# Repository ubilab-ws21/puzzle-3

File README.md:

# Puzzle 3

## Contents
- [Puzzle overview](#puzzle-overview)
- [Repo Structure](#repo-structure)
- [Fitting the Puzzle into the story](#fitting-the-puzzle)
- [Puzzle description](#puzzle-description)
	- [Puzzle Part 1](#Puzzle-1)
	- [Puzzle Part 2](#Puzzle-2)
	- [Puzzle Part 3](#Puzzle-3)
- [MQTT Topics/Specification](#MQTT-Spec)
- [Documents](#documents)

## Puzzle overview

The central role of our puzzle plays a "radio".
The radio consists of a touchscreen display, a speaker, a module to play sound from an sd card, three encoders for tuning as well as one for the volume. The devices are all connected to a ESP32 WROOM Development kit. 
Final aim of the puzzle is to retrieve the so-called "green code" which is needed in a combination to restart the final server, i.e. to succeed in playining the Escape Room. 
It is to be discussed if the radio will maybe deliver more information, e.g. hints for the next puzzle (Morse-Code sound to open the server room door). 
The green code will eventually be displayed on the radio screen, once all the radio-related puzzles have been solved. The puzzles to be solved include the correct positioning of the three encoders which results in a change of the radio station.
The new channel also comes with a new radio display screen. Solving a word game now leads to the final green code. 

## Repo Structure

This repository is structured in the following way:
- datasheets contains all interesting datasheets
- designs contains eagle designs
- code contains the code
- notes cotains all notes from lectures and meetings

## Fitting the Puzzle into the story

The radio belongs to the hobby funker and former power distribution worker Ferdi. 
He has been fired a few years ago due to automatisation and digitalization of the distribution center. Ever since he has been fired, the work in the control room had been done autonomously. Ferdi has always predicted that the full autonoumous room can be dangerous in the future because nobody knows how to fix things if something goes wrong. 

## Puzzle Description 

### Puzzle Part 1 

There is an antenna hidden in the room. When the radio turns on, there is nothing but noise to hear. The players need to find the antenna and plug it into a socket one can find at the radio. This will trigger a button. Also, the correct positioning of the antenna makes a difference which is observed by an encoder insider the radio case. When both is fine, there will be no noise anymore and an emergency broadcast can be heard nicely.

### Puzzle Part 2
A world map is placed in the room. There are three colored pins placed on three diffeents countries pinned on the map. Meanwhile, the screen of the radio shows a three slider bars in the same colors, where the values of each bar can be changed with a correspondingly colored encoder.
Both the radio and the world map belong to the former control room worker, i.e. his name is printed on both the radio case and the world map.
The emergency broadcast plays repeatedly. 
The players must look at the pins on the map, extract the difference of the locations to the greenwich mean time (=delta) and turn the correspondingly colored encoders so that the sliding bars have the deltas as values. When this is done, the Emergency broadcast stops, and instead the voice of the former control room worker, a hobby radio operator, arises. Also the screen changed. The puzzle is solved.

### Puzzle Part 3
In the recording, the former control room worker repeatedly says that he has forseen this and that going away from manual control to autonoumously controlled distribution was a bad choice. 
The screen shows a word puzzle, where it is not clear yet how it looks exactly. From the voice from the radio guy it becomes clear how to solve the puzzle.
After the puzzle was solved, the screen changes again and shows the code which is needed for the next puzzle of the next group (code for opening the door via light bulbs)

## MQTT Topics/Specification

| Topic | Description | Payload | Reset-Value | Subscriber | Publisher |
| :--:	| :---------: | :------:| :---------: |:--------: | :--------:|
| 3/gamecontrol| Control the radio: which puzzle state is currently in play | Enum(Gamecontrol) | idle | radio, operator | radio, operator | 
| 3/antenna/orientation | gives information if the angle of the antenna correct | boolean | false | operator | radio |
| 3/map/knob1 | gives information whether knob1 is in correct position | boolean | false | operator | radio |
| 3/map/knob2 | gives information whether knob2 is in correct position | boolean | false | operator | radio |
| 3/map/knob3 | gives information whether knob3 is in correct position | boolean | false | operator | radio |
| 3/touchgame/trialCount | gives information about the trails the group already had | int | 0 | operator | radio |
| 3/touchgame/displayTime | the game can either be set in easy or hard mode | boolean | false | radio | operator |

3/gamecontrol maybe splitted to received and sended topic. For now we wait for feedback by the operator

| Enum(gameControl) | Description | Subscriber | Publisher |
| :---------------: | :---------: | :--------: | :-------: |
| idle | Radiopuzzle is waiting in idle mode to be started by operator | radio | operator |
| antenna | antenna game is started by operator | radio | operator |
| antennaFinished | antenna game is finished | operator | radio |
| map | map game is started by operator | radio | operator |
| mapFinished | map game is finished | operator | radio |
| touchgame | touchgame is started by operator | radio | operator |
| touchgameFinished | touchgame is finished | operator | radio |
| finished | radio game is finished | operator | radio |

| int(trailCount) | Description |
| :-------------: | :---------: |
| ++ | everytime the game is failed, the trialcounter is increased |

#Topic: 3/gamecontrol

Description: Control the radio: which puzzle state is currently in play

Payload: Enum(Gamecontrol)

Reset-Value: Idle

Enum Values:

# Idle: Radio puzzle is waiting in Idle mode to be started
- Publisher: Operator: set the third puzzle in idle mode
- Subscriber: Radio: receive to stay in idle mode

- antenna: antenna game is started
	Operator: start the first part of the puzzle
	radio: receive to start the puzzle with antenna game
- antennaFinished: antenna game is finished
	Operator: receive updates on the gamestatus
	radio: update once the game is finished

- map: map game is played
	Operator: start the second part of the puzzle
	radio: receive to start the second part of the puzzle
- mapFinished: map game is finished
	Operator: receive updates on the gamestatus
	radio: update once the game is finished

- touchgame: touchgame is played
	Operator: start the third part of the puzzle
	radio: receive to start the third part of the puzzle
- touchgameFinished: touchgame is finished
	Operator: receive updates on the game status
	radio: update once the game is finished

- finished: puzzle 3 is solved
	Operator: set the third puzzle in finished mode
	radio: receive to get in finished mode

<!--Topic: 3/antenna/plugStatus

#Description: gives information about the antenna

% Payload: boolean

Reset-Value: false
	Radio: update if antenna is plugged in
	Operator: receive updates on the antenna-->
	
Topic: 3/antenna/orientation

Description: gives information about the antenna orientation, should the operator know about the randomisation of the required postion?

Payload: int[0-23] or boolean
	Radio: update if antenna is set up in the correct direction
	Operator: receive updates on the antenna orientation

Topic: 3/map/knob1

Description: Control/Check the first knob

Playload: boolean

Reset-Value: false
	Radio: update if the the first knob/color reaches/leaves the correct postion
	Operator: receive updates on the first knob

Topic: 3/map/knob2

Description: Control/Check the second knob

Playload: boolean

Reset-Value: false
	Radio: update if the the second knob/color reaches/leaves the correct postion
	Operator: receive updates on the second knob

Topic: 3/map/knob3

Description: Control/Check the third knob

Playload: boolean

Reset-Value: false
	Radio: update if the the third knob/color reaches/leaves the correct postion
	Operator: receive updates on the third knob

Topic: 3/touchgame/trialCount

Description: Sends the number of trials to the operator 

Payload: int

Reset-Value is 0
	Radio: Update the trial number after each failed attempt
	Operator: receive updates on the failed attempts
	
Topic: 3/touchgame/displayTime

Description: Operator sets the time to easy or hard mode

Payload: boolean

Reset-Value: false
	Radio: receive updates on mode setting
	Operator: set mode for puzzle

Description: needs some discussion what should be updated to the operator

## Documents
The datasheets can be found in the datasheets directory

## Notes
The board with the ICs, placed on the bottom of the radio case inside, should be 9cm x 13cm long.
Software game: We only have one rectangle. By placing the blue rectangle on a letter and touching it, the rectangle and the letter will go to the next free location in the password space.

Next Tasks - 23.01
- Driver Board an case anbringen
- MQTT auf ESP32 fertig implementieren

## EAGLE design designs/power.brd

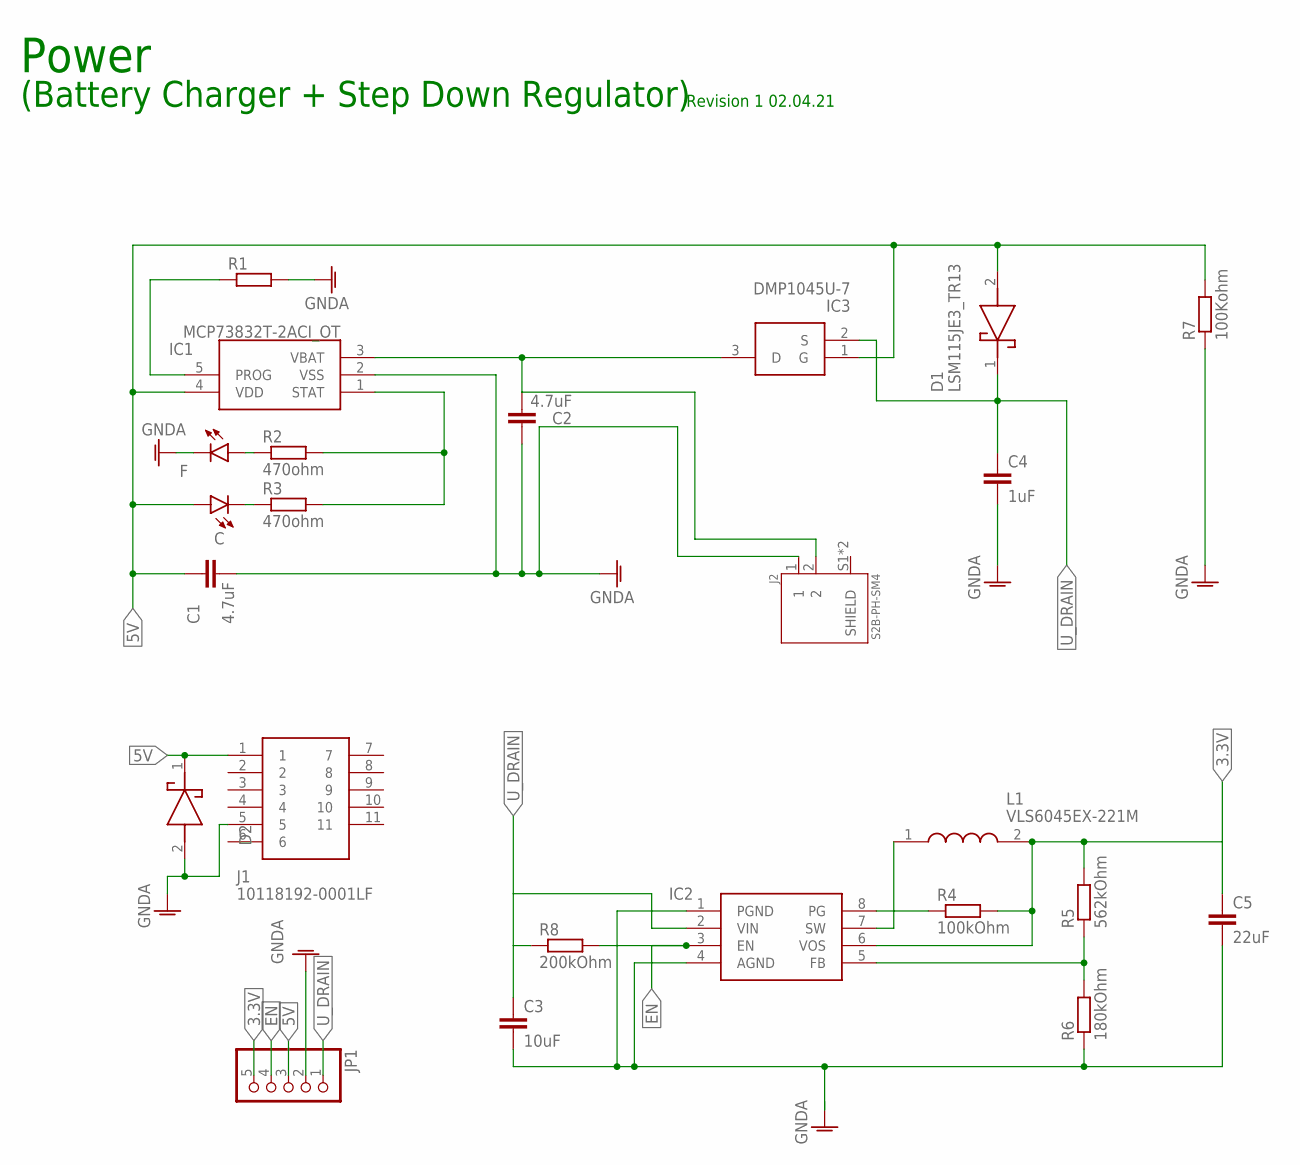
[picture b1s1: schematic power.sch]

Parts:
C: LED_1206SMT1206; 1206
C1, C2: 4.7uF; C1206
C3: 10uF; C1206
C4: 1uF; C0805
C5: 22uF; C0805K
D1, D2: LSM115JE3_TR13; DIOM5436X330N
F: LED_1206SMT1206; 1206
IC1: MCP73832T-2ACI_OT; SOT95P270X145-5N
IC2: TPS62160DGKR; SOP65P490X110-8N
IC3: DMP1045U-7; SOT96P240X100-3N
J1: 10118192-0001LF; 101181920001LF
J2: S2B-PH-SM4; JST_S2B-PH-SM4-TB(LF)(SN)
JP1: PINHD-1X5; 1X05
L1: VLS6045EX-221M; INDPM6060X450N
R1: R-EU_805R0805; R0805
R2, R3: 470ohm; R0805
R4: 100kOhm; R0805
R5: 562kOhm; R0805
R6: 180kOhm; R0805
R7: 100Kohm; R0805
R8: 200kOhm; R0805

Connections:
3.3V: C5.1, IC2.6 (VOS), JP1.5, L1.2, R4.2, R5.2
5V: C.A, C1.1, D1.2 (A), D2.1 (K), IC1.4 (VDD), IC3.1 (G), J1.1, JP1.3, R7.2
EN: IC2.3 (EN), JP1.4, R8.2
FB: IC2.5 (FB), R5.1, R6.2
GNDA: C1.2, C2.1, C3.2, C4.2, C5.2, D2.2 (A), F.C, IC1.2 (VSS), IC2.1 (PGND), IC2.4 (AGND), J1.5, J2.1, JP1.2, R1.2, R6.1, R7.1
unnamed: IC1.5 (PROG), R1.1
unnamed: F.A, R2.1
unnamed: C.C, R3.1
PG: IC2.8 (PG), R4.1
STAT: IC1.1 (STAT), R2.2, R3.2
SW: IC2.7 (SW), L1.1
U_DRAIN: C3.1, C4.1, D1.1 (K), IC2.2 (VIN), IC3.2 (S), JP1.1, R8.1
VBAT: C2.2, IC1.3 (VBAT), IC3.3 (D), J2.2

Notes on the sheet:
Power
(Battery Charger + Step Down Regulator)
Revision 1 02.04.21

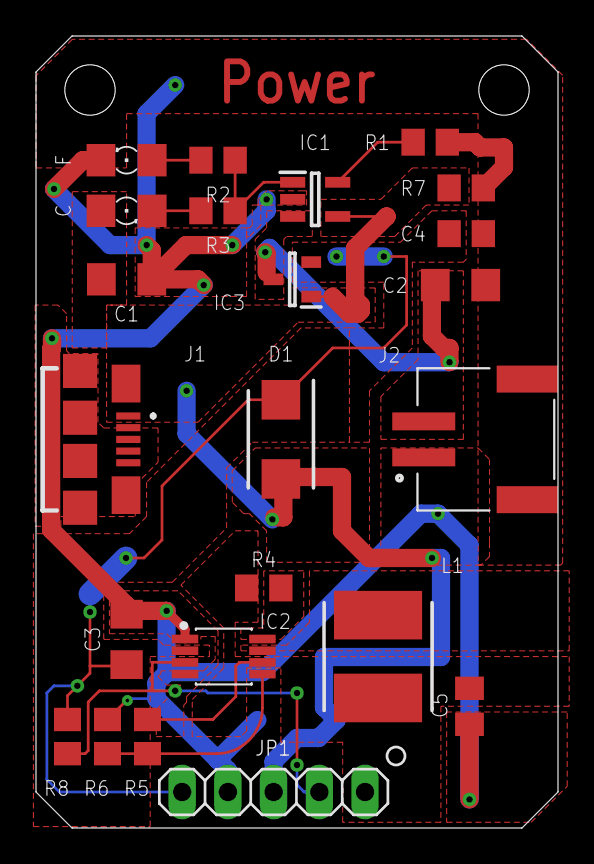
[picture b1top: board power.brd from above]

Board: 2 copper layers, 29.0 x 44.0 mm, 24 parts (1 on the bottom side), 13 nets.

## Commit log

2021-11-08 Story Update after discussion of 4.11.21 (KW44)
    initial commit of the story description.
2021-11-08 Initial commit of Puzzle Idea
    commit of fundamental idea of Puzzle 3
2021-11-10 added yesterday's notes. Details about our puzzle and a first, rough BOM
2021-11-11 updated BOM
2021-11-25 notes from 25.11, also another overview of our puzzle
2021-12-01 First Readme changes
2021-12-01 new structured directory
2021-12-01 Changed Readme title
2021-12-01 added datasheets
2021-12-01 renamed datasheets
2021-12-01 added eagle files
2021-12-01 changed readme
2021-12-02 changed names of datasheets
2021-12-02 some more readme stuff
2021-12-03 First working version for display: Example code from library. Touched not touched yet^^
2021-12-03 edited Readme
2021-12-03 small correction
2021-12-03 changed schematic for display in eagle
2021-12-07 Minimum touchscreen demo with calibration.
2021-12-07 added the first code for the Audio and more Datasheets of ESP32
2021-12-07 functioning AudioSetupTest.ino
2021-12-08 added EEPROM support and included encoder.
2021-12-09 added first steps for encoder handling and sliding bars
2021-12-09 updated mainboard schematic
2021-12-13 added Library for DFPlayerMini
2021-12-13 added DFPlayer to mainboard schematic
2021-12-15 started implementing a game for the third puzzle with solution word MANUAL. It works so far but the goal is not implemented yet
2021-12-16 uploaded stl of PinHead-EncoderKnob
2022-01-07 added all 3DModels and slice examples
2022-01-07 delted 3D-Model
2022-01-09 Added Puzzle-Control/MQTT Prototype
2022-01-11 merged music player into existing code
2022-01-11 added first screen. but noise not nice yet
2022-01-12 added first screen (noise). Screen is removed by encoder event until we have a working antenna
2022-01-12 added usage of a second encoder, general settings
2022-01-12 added text and labelling of bars
2022-01-12 corrected term mistake
2022-01-13 some changes and fixed bug in set_encoder_handle function
2022-01-13 added letter placeholder rectangles in the bottom
2022-01-13 placeholders are now redrawn properly
2022-01-13 cleaning
2022-01-13 solved touch error
2022-01-13 added 3rd encoder
2022-01-13 added all numbers to sliding bar screen
2022-01-13 implemented random letter generation
2022-01-13 next tasks
2022-01-14 Update README.md
    added mqtt topics
2022-01-16 removed a few bugs and added goal stage for rectangle puzzle
2022-01-16 removed bug in random number generation
2022-01-17 nicer view of password space
2022-01-17 changed the way the password area is presented
2022-01-17 added show button, removed encoder3 function. This is done with show button now instead
2022-01-17 added show button label: now show button can be pressed up tp 3 times, afterwards the game is reset
2022-01-17 changed return type of letter generation function, according to last commit
2022-01-17 added title of rectangle game, changed direction of rectangle movements with encoder trigger
2022-01-17 changed final screen: added random code
2022-01-17 minor changes
2022-01-17 added additional encoders and connected them to the ESP
2022-01-17 changed state machine: state 3
2022-01-19 updated and added 3D print files
2022-01-19 added Lasercut files
2022-01-19 deleted outdated files
2022-01-19 changed directory name
2022-01-19 added 3D model of Radio
2022-01-19 Display circuit mount test
2022-01-20 added volume control encoder and functioning
2022-01-21 update manufacturing file
2022-01-22 Update README.md
    worked on MQTT-Spec, added payload & reset values
2022-01-23 Update README.md
    added tasks for the week
2022-01-23 added reset button
2022-01-23 fixed volume change bug
2022-01-25 Create MQTT.md
    Specification of the MQTT-Topics used for Puzzle 3
2022-01-25 updated MQTT project file to be ready to include puzzle
2022-01-26 added audio, new test print stl.
2022-01-26 new smallTestprint
2022-01-26 added 3D print antenna Support file
2022-01-26 new antenna support
2022-01-26 other versions
2022-01-26 antenna support v3
2022-01-27 many changes, including frequency display und select button for game 1, and letter removal for game 2
2022-01-27 nicer select button, no reset after selecting frequency, error msg
2022-01-27 removed bug for removing letters at first action.
2022-01-27 fixed hardware bug
2022-01-27 added support for JSON-formatted control of the puzzle started to work on MQTT-response to operator
2022-01-27 Create hints.md
    hints for puzzle 3
2022-01-31 new Files
2022-01-31 some random changes, e.g. with antenna, still in progress
2022-01-31 Update MQTT.md
    Reduced the amount of topics & added the topics for the hint-system
2022-01-31 Update MQTT.md
    quickfix of an error in table
2022-01-31 first adaptions for MQTT - no waiting for touch event anymore
2022-01-31 updated TopDisplayHpusing
2022-01-31 audio updates
2022-01-31 new Antenna
2022-01-31 Antenna update
2022-01-31 added hint system function
2022-01-31 outsourced functions in two new c++ files for better overview. Added states for antenna positions
2022-01-31 completed antenna position checker
2022-01-31 some more changes, e.g. changed rectangle name
2022-01-31 hopefully almost removed the bug with the triangle in the frequency game
2022-01-31 started to implement MQTT in the puzzle-statemachine
2022-01-31 removed bug for removing letters, workaround
2022-02-01 added hint-system communication added support for operator controlled or puzzlecontrolled state/puzzlechange
2022-02-01 included cursor with 3rd encoder
2022-02-01 only typo
2022-02-01 integrated idle state where screen is asleep
2022-02-03 removed a few more bugs
2022-02-03 added comments and function descriptions, removed some unneeded functions and vars
2022-02-03 added define for volume2
2022-02-03 added header
2022-02-03 some adaptions to integrate MQTT
2022-02-03 corrected mistake in MQTT message
2022-02-03 Message size increased (MWTT)
2022-02-03 added encoder filters
2022-02-06 changed hint-system according to provided requirements
2022-02-07 added hour display on last screen
2022-02-07 changed login game: now you can touch anywhere in the letter section to bring a letter to the password section
2022-02-07 Revert "changed hint-system according to provided requirements"
    This reverts commit 95b610a824ab029964c2c20212dc70f59835ce79.
2022-02-07 re-initialized hint system
2022-02-07 only some auto-formatting for the whole file
2022-02-07 removed tcp server connection to make current time getter work. Also restructured some stuff in relation to the time getter
2022-02-07 bug fix: correct hour display
2022-02-07 added development mode: usually idle state can only go to antenna state by Operator via MQTT. But in development mode, we can use the encoders for this
2022-02-07 no development mode for now
2022-02-08 small bug fixes: hint system and clock in done state
2022-02-08 changed control of puzzle - operator should not be able anymore to trigger game twice moved backcommunication/hint-communication - should work without operator call
2022-02-08 added possibility to play final message by operator call
2022-02-10 some more bug fixes
2022-02-10 bug fix: display is black in idle mode now.
2022-02-10 fixed volume bug final state
2022-02-10 disabled loop in final state
2022-02-10 removed double trigger when entering the login game
